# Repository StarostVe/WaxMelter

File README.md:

# WaxMelter
Induction wax melter for hot-waxing bike chains

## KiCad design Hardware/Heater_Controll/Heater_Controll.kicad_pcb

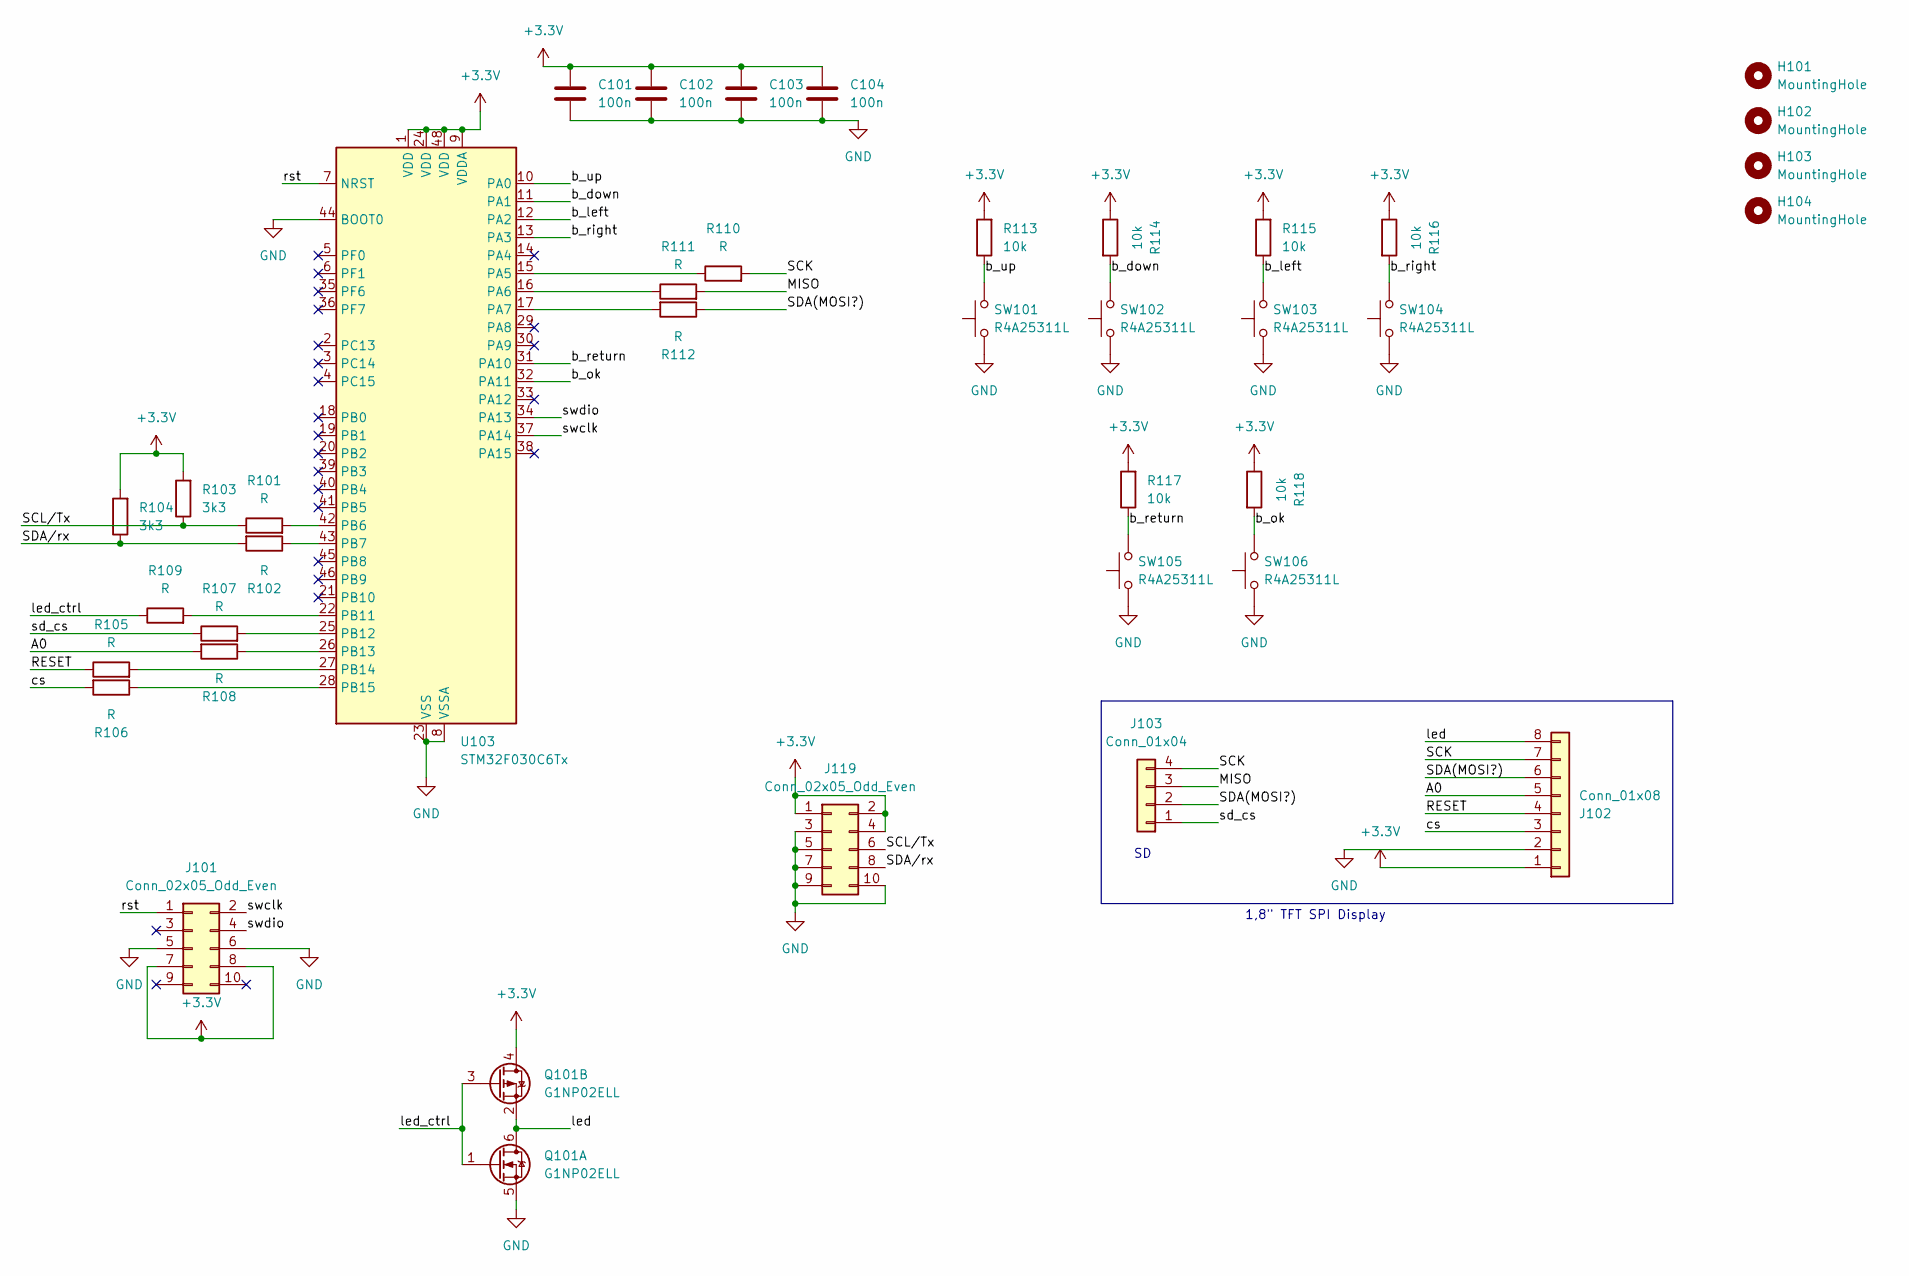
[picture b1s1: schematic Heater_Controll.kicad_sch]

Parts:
C101, C102, C103, C104: 100n; C_0603_1608Metric
H101, H102, H103, H104: MountingHole; MountingHole_3.2mm_M3_DIN965
J101, J119: Conn_02x05_Odd_Even; IDC-Header_2x05_P2.54mm_Vertical_SMD
J102: Conn_01x08; PinHeader_1x08_P2.54mm_Vertical
J103: Conn_01x04; PinHeader_1x04_P2.54mm_Vertical
Q101: G1NP02ELL; TSOT-23-6
R101, R102, R105, R106, R107, R108, R109, R110, R111, R112: R; R_0603_1608Metric
R103, R104: 3k3; R_0603_1608Metric
R113, R114, R115, R116, R117, R118: 10k; R_0603_1608Metric
SW101, SW102, SW103, SW104, SW105, SW106: R4A25311L
U103: STM32F030C6Tx; LQFP-48_7x7mm_P0.5mm

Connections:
+3.3V: C101.1, C102.1, C103.1, C104.1, J101.7, J101.8, J102.1, J119.1, J119.2, J119.4, Q101.4 (D), R103.2, R104.2, R113.2, R114.1, R115.2, R116.1, R117.2, R118.1, U103.1 (VDD), U103.9 (VDDA), U103.24 (VDD), U103.48 (VDD)
/A0: J102.5, R108.2
/MISO: J103.3, R111.2
/RESET: J102.4, R105.1
/SCK: J102.7, J103.4, R110.2
/SCL/Tx: J119.6, R101.1, R103.1
/SDA(MOSI?): J102.6, J103.2, R112.1
/SDA/rx: J119.8, R102.2, R104.1
/b_down: R114.2, SW102.2, U103.11 (PA1)
/b_left: R115.1, SW103.2, U103.12 (PA2)
/b_ok: R118.2, SW106.2, U103.32 (PA11)
/b_return: R117.1, SW105.2, U103.31 (PA10)
/b_right: R116.2, SW104.2, U103.13 (PA3)
/b_up: R113.1, SW101.2, U103.10 (PA0)
/cs: J102.3, R106.2
/led: J102.8, Q101.2 (S), Q101.6 (D)
/led_ctrl: Q101.1 (G), Q101.3 (G), R109.1
/rst: J101.1, U103.7 (NRST)
/sd_cs: J103.1, R107.1
/swclk: J101.2, U103.37 (PA14)
/swdio: J101.4, U103.34 (PA13)
GND: C101.2, C102.2, C103.2, C104.2, J101.5, J101.6, J102.2, J119.3, J119.5, J119.7, J119.9, J119.10, Q101.5 (S), SW101.1, SW102.1, SW103.1, SW104.1, SW105.1, SW106.1, U103.8 (VSSA), U103.23 (VSS), U103.44 (BOOT0), U103.47 (VSS)
unnamed: R110.1, U103.15 (PA5)
unnamed: R111.1, U103.16 (PA6)
unnamed: R112.2, U103.17 (PA7)
unnamed: R101.2, U103.42 (PB6)
unnamed: R102.1, U103.43 (PB7)
unnamed: R109.2, U103.22 (PB11)
unnamed: R107.2, U103.25 (PB12)
unnamed: R108.1, U103.26 (PB13)
unnamed: R105.2, U103.27 (PB14)
unnamed: R106.1, U103.28 (PB15)

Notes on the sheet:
1,8" TFT SPI Display

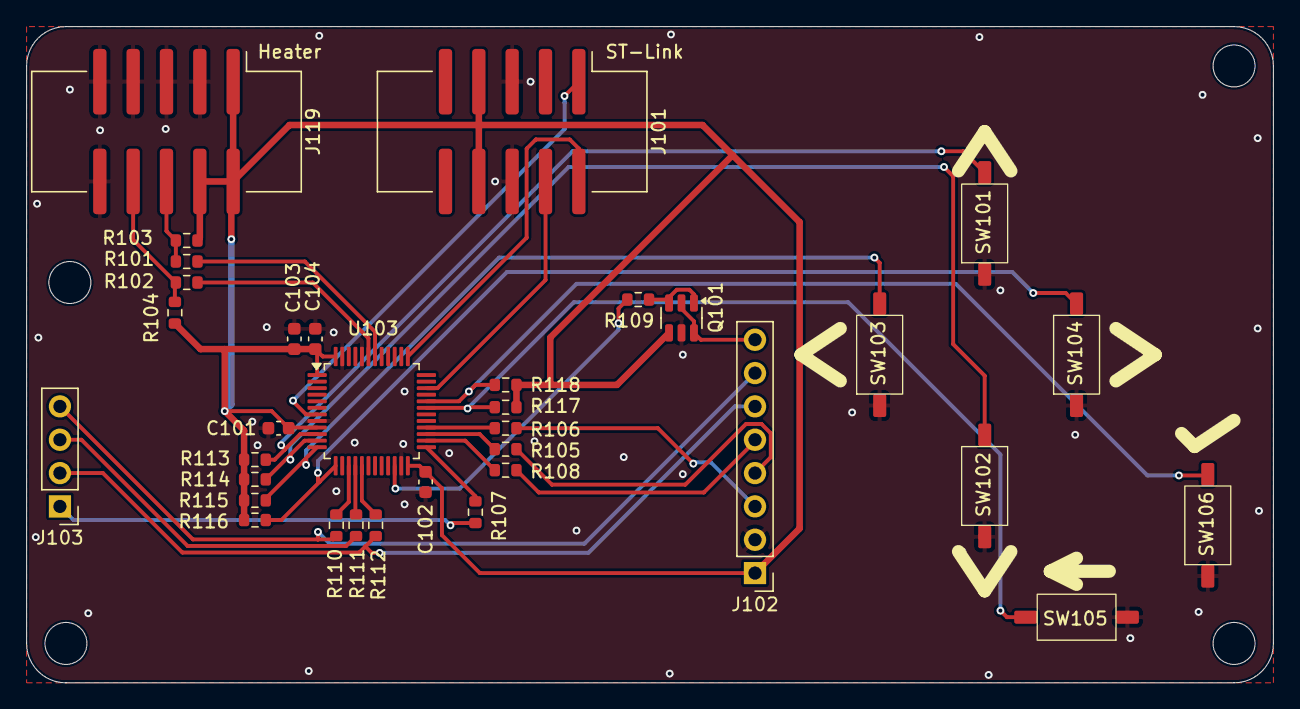
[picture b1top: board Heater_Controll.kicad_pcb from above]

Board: 2 copper layers, 95.0 x 50.0 mm, 38 parts (0 on the bottom side), 32 nets.

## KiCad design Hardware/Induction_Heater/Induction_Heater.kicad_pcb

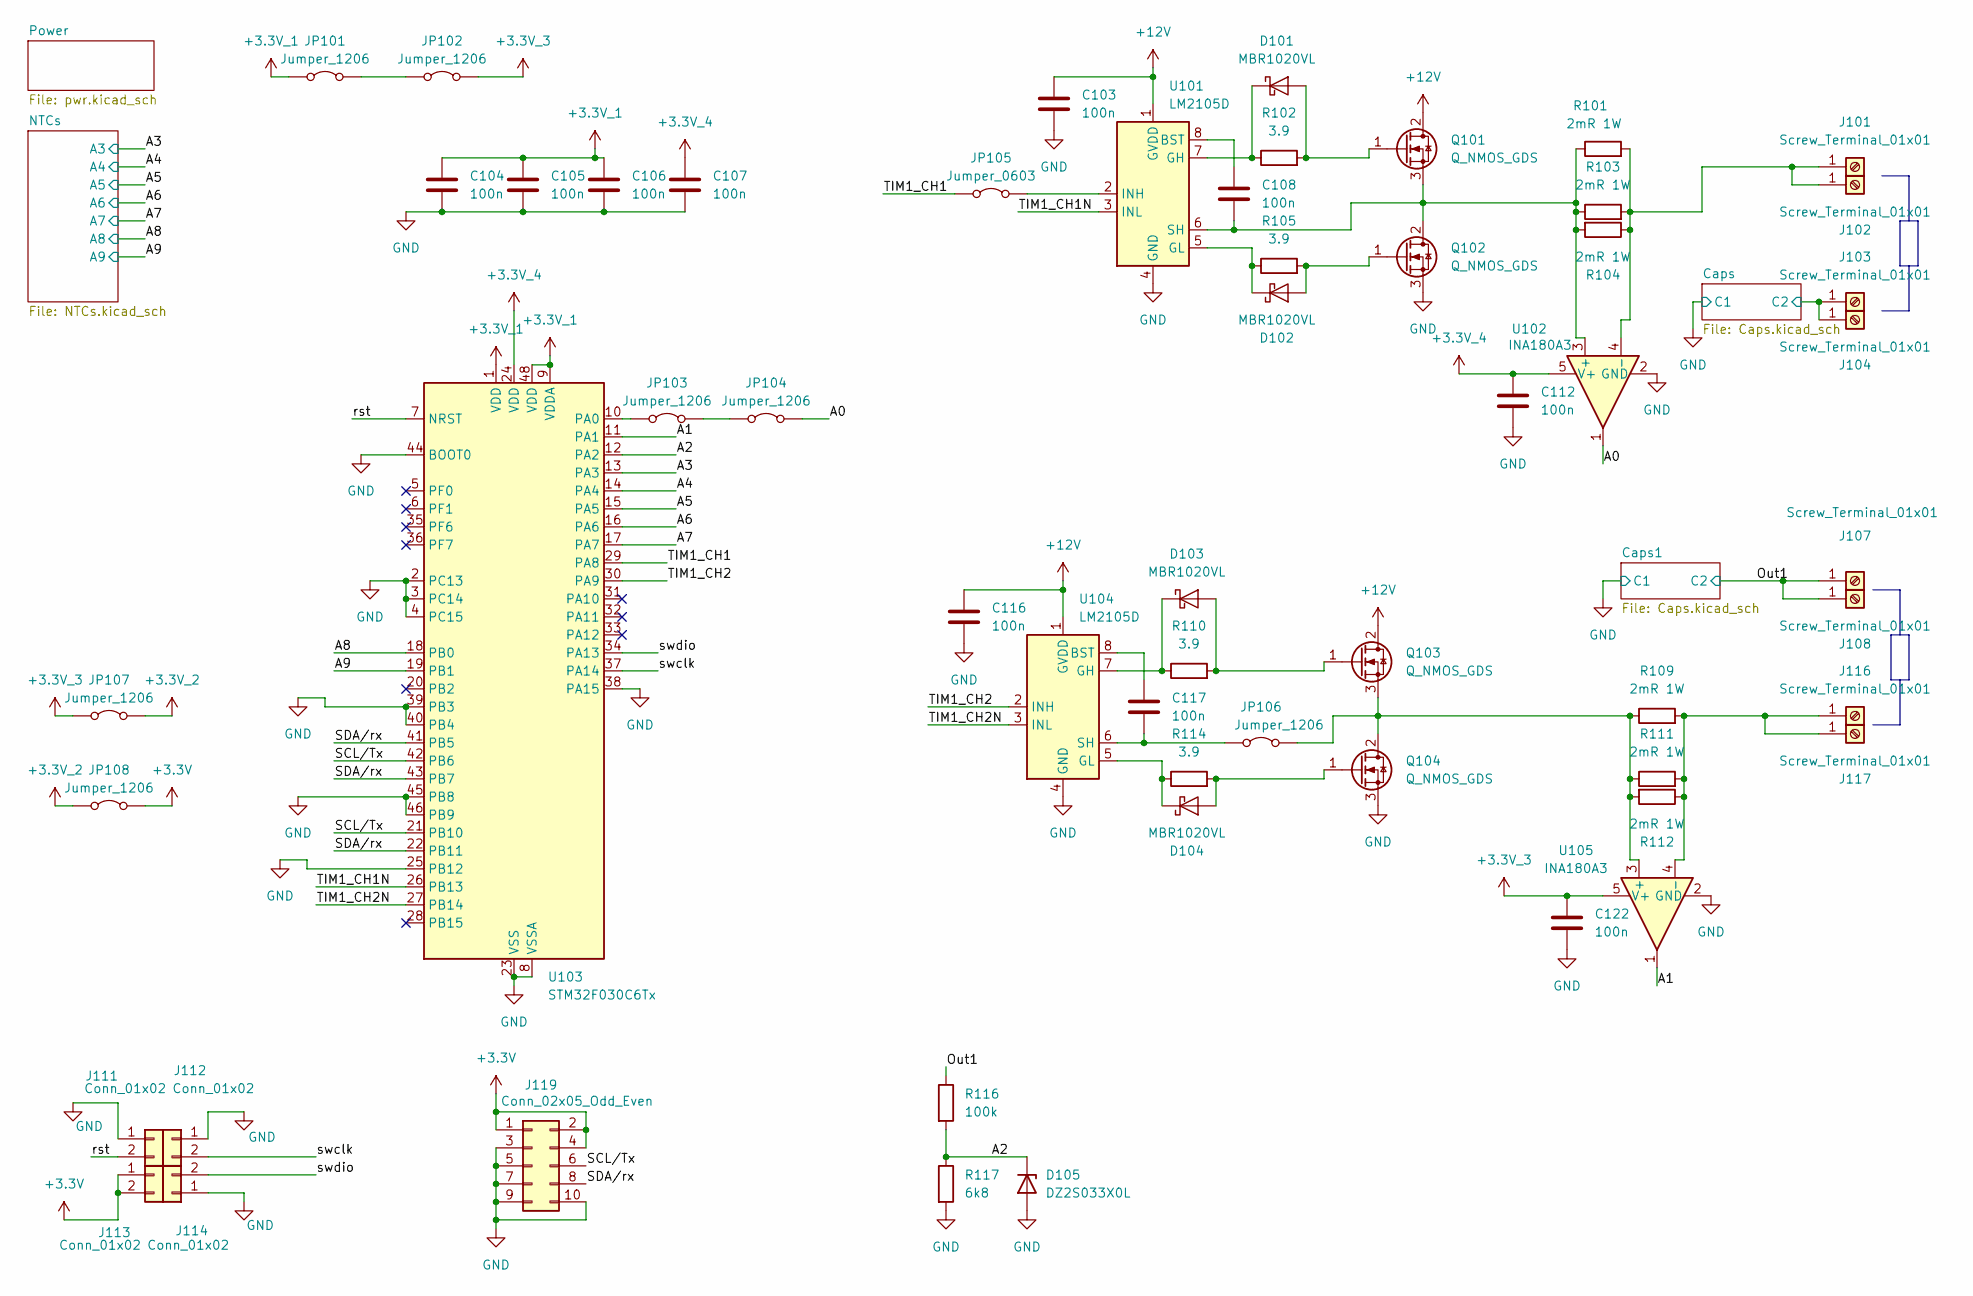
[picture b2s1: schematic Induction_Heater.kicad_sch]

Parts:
C103, C104, C105, C106, C107, C108, C112, C116, C117, C122: 100n; C_0603_1608Metric
D101, D102, D103, D104: MBR1020VL; D_SOD-123F
D105: DZ2S033X0L; D_SOD-523
J101, J102, J103, J104, J107, J108, J116, J117: Screw_Terminal_01x01; TS34056055-0440
J111, J112, J113, J114: Conn_01x02; PinHeader_1x02_P2.54mm_Vertical_SMD_Pin1Left
J119: Conn_02x05_Odd_Even; IDC-Header_2x05_P2.54mm_Vertical_SMD
JP101, JP102, JP103, JP104, JP106, JP107, JP108: Jumper_1206; R_1206_3216Metric
JP105: Jumper_0603; R_0603_1608Metric
Q101, Q102, Q103, Q104: Q_NMOS_GDS; TO-252-2
R101, R103, R104, R109, R111, R112: 2mR 1W; R_1206_3216Metric
R102, R105, R110, R114: 3.9; R_0603_1608Metric
R116: 100k; R_0603_1608Metric
R117: 6k8; R_0603_1608Metric
U101, U104: LM2105D; SOIC-8_3.9x4.9mm_P1.27mm
U102, U105: INA180A3; SOT-23-5
U103: STM32F030C6Tx; LQFP-48_7x7mm_P0.5mm

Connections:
+3.3V: J113.1, J113.2, J119.1, J119.2, J119.4, JP108.2 (B); also elsewhere on the board
+3.3V_1: C104.1, C105.1, C106.1, JP101.1 (A), U103.1 (VDD), U103.9 (VDDA), U103.48 (VDD)
+3.3V_2: JP107.2 (B), JP108.1 (A); also elsewhere on the board
+3.3V_3: C122.1, JP102.2 (B), JP107.1 (A), U105.5 (V+); also elsewhere on the board
+3.3V_4: C107.1, C112.1, U102.5 (V+), U103.24 (VDD); also elsewhere on the board
+12V: C103.1, C116.1, Q101.2 (D), Q103.2 (D), U101.1 (GVDD), U104.1 (GVDD); also elsewhere on the board
/A0: JP104.2 (B), U102.1
/A1: U103.11 (PA1), U105.1
/A2: D105.1 (K), R116.2, R117.1, U103.12 (PA2)
/A3: U103.13 (PA3); also elsewhere on the board
/A4: U103.14 (PA4); also elsewhere on the board
/A5: U103.15 (PA5); also elsewhere on the board
/A6: U103.16 (PA6); also elsewhere on the board
/A7: U103.17 (PA7); also elsewhere on the board
/A8: U103.18 (PB0); also elsewhere on the board
/A9: U103.19 (PB1); also elsewhere on the board
/Caps/C2: J103.1, J104.1; also elsewhere on the board
/Out1: J107.1, J108.1, R116.1; also elsewhere on the board
/SCL/Tx: J119.6, U103.21 (PB10), U103.42 (PB6)
/SDA/rx: J119.8, U103.22 (PB11), U103.41 (PB5), U103.43 (PB7)
/TIM1_CH1: JP105.1 (A), U103.29 (PA8)
/TIM1_CH1N: U101.3 (INL), U103.26 (PB13)
/TIM1_CH2: U103.30 (PA9), U104.2 (INH)
/TIM1_CH2N: U103.27 (PB14), U104.3 (INL)
/rst: J111.2, U103.7 (NRST)
/swclk: J112.2, U103.37 (PA14)
/swdio: J114.2, U103.34 (PA13)
GND: C103.2, C104.2, C105.2, C106.2, C107.2, C112.2, C116.2, C122.2, D105.2 (A), J111.1, J112.1, J114.1, J119.3, J119.5, J119.7, J119.9, J119.10, Q102.3 (S), Q104.3 (S), R117.2, U101.4 (GND), U102.2 (GND), U103.2 (PC13), U103.3 (PC14), U103.4 (PC15), U103.8 (VSSA), U103.23 (VSS), U103.25 (PB12), U103.38 (PA15), U103.39 (PB3), U103.40 (PB4), U103.44 (BOOT0), U103.45 (PB8), U103.46 (PB9), U103.47 (VSS), U104.4 (GND), U105.2 (GND); also elsewhere on the board
unnamed: D101.2 (A), Q101.1 (G), R102.2
unnamed: D101.1 (K), R102.1, U101.7 (GH)
unnamed: D102.2 (A), Q102.1 (G), R105.2
unnamed: D102.1 (K), R105.1, U101.5 (GL)
unnamed: D103.2 (A), Q103.1 (G), R110.2
unnamed: D103.1 (K), R110.1, U104.7 (GH)
unnamed: D104.2 (A), Q104.1 (G), R114.2
unnamed: D104.1 (K), R114.1, U104.5 (GL)
unnamed: J101.1, J102.1, R101.2, R103.2, R104.1, U102.4 (-)
unnamed: J116.1, J117.1, R109.2, R111.2, R112.1, U105.4 (-)
unnamed: JP101.2 (B), JP102.1 (A)
unnamed: JP103.1 (A), U103.10 (PA0)
unnamed: JP103.2 (B), JP104.1 (A)
unnamed: JP105.2 (B), U101.2 (INH)
unnamed: C117.2, JP106.1 (A), U104.6 (SH)
unnamed: JP106.2 (B), Q103.3 (S), Q104.2 (D), R109.1, R111.1, R112.2, U105.3 (+)
unnamed: C108.2, Q101.3 (S), Q102.2 (D), R101.1, R103.1, R104.2, U101.6 (SH), U102.3 (+)
unnamed: C108.1, U101.8 (BST)
unnamed: C117.1, U104.8 (BST)

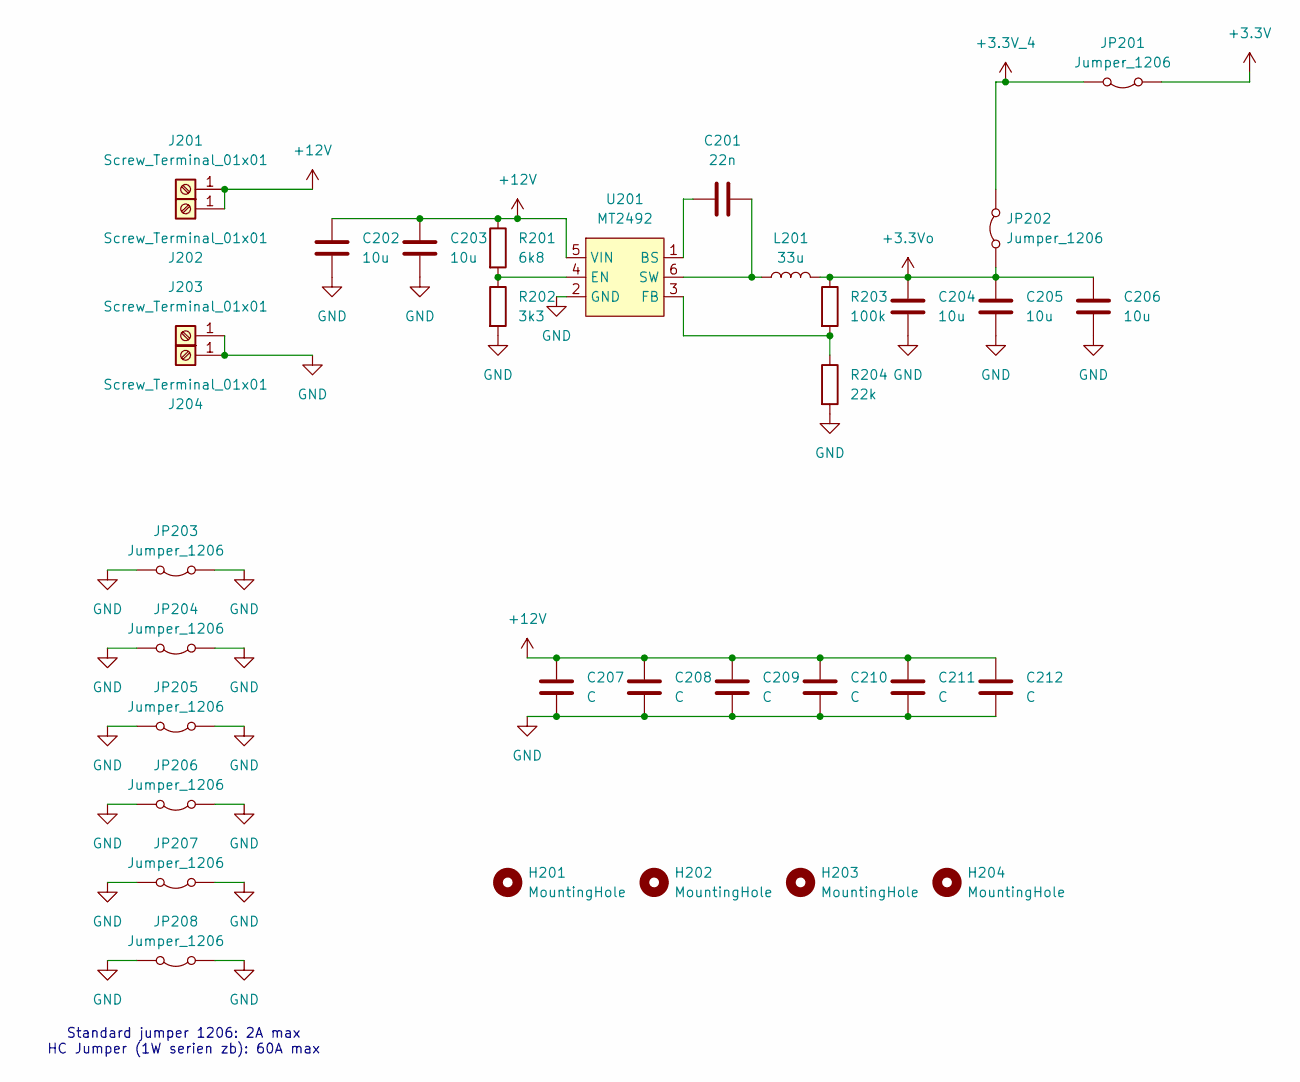
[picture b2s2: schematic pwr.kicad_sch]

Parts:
C201: 22n; C_0603_1608Metric
C202, C203, C204, C205, C206: 10u; C_0603_1608Metric
C207, C208, C209, C210, C211, C212: C; C_1206_3216Metric
H201, H202, H203, H204: MountingHole; MountingHole_3.2mm_M3_DIN965
J201, J202, J203, J204: Screw_Terminal_01x01; TS34056055-0440
JP201, JP202, JP203, JP204, JP205, JP206, JP207, JP208: Jumper_1206; R_1206_3216Metric
L201: 33u; L_APV_ANR4030
R201: 6k8; R_0603_1608Metric
R202: 3k3; R_0603_1608Metric
R203: 100k; R_0603_1608Metric
R204: 22k; R_0603_1608Metric
U201: MT2492; SOT-23-6

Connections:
+3.3V: JP201.1 (A); also elsewhere on the board
+3.3V_4: JP201.2 (B), JP202.2 (B); also elsewhere on the board
+3.3Vo: C204.1, C205.1, C206.1, JP202.1 (A), L201.2, R203.1
+12V: C202.1, C203.1, C207.1, C208.1, C209.1, C210.1, C211.1, C212.1, J201.1, J202.1, R201.1, U201.5 (VIN); also elsewhere on the board
GND: C202.2, C203.2, C204.2, C205.2, C206.2, C207.2, C208.2, C209.2, C210.2, C211.2, C212.2, J203.1, J204.1, JP203.1 (A), JP203.2 (B), JP204.1 (A), JP204.2 (B), JP205.1 (A), JP205.2 (B), JP206.1 (A), JP206.2 (B), JP207.1 (A), JP207.2 (B), JP208.1 (A), JP208.2 (B), R202.2, R204.2, U201.2 (GND); also elsewhere on the board
unnamed: C201.1, U201.1 (BS)
unnamed: R201.2, R202.1, U201.4 (EN)
unnamed: R203.2, R204.1, U201.3 (FB)
unnamed: C201.2, L201.1, U201.6 (SW)

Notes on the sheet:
Standard jumper 1206: 2A max HC Jumper (1W serien zb): 60A max

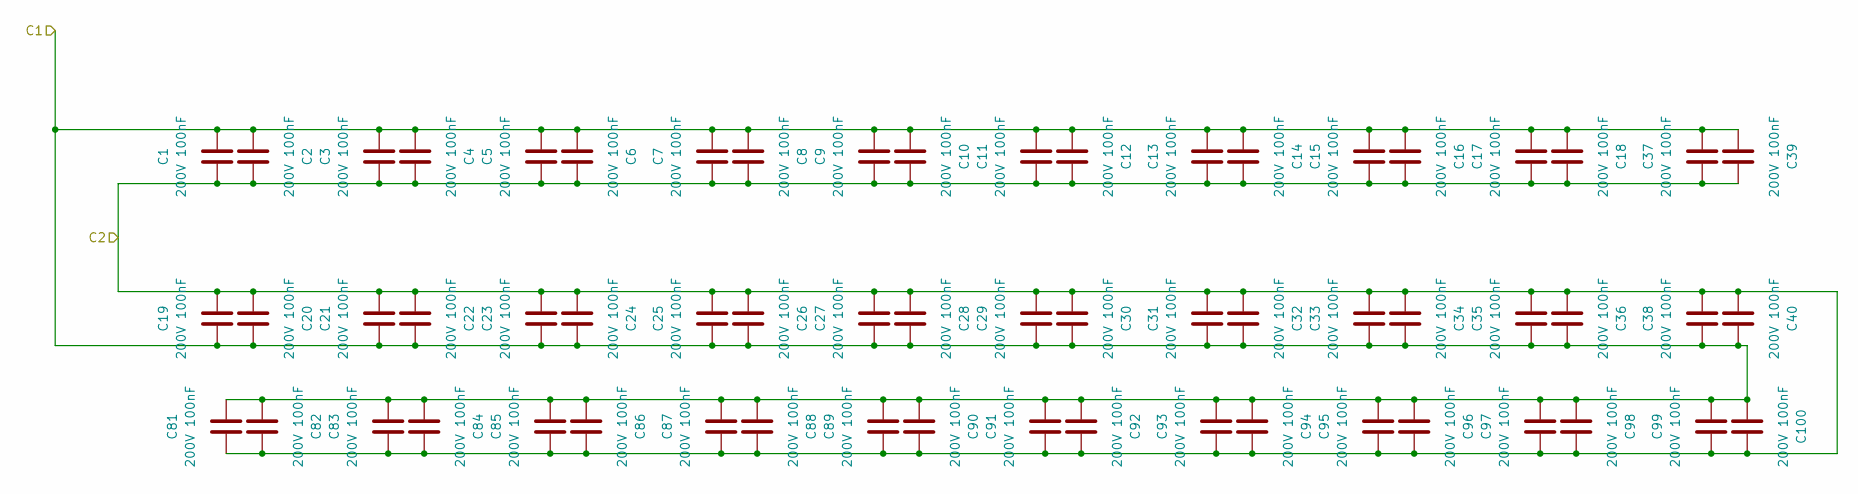
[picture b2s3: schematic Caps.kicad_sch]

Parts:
C1, C2, C3, C4, C5, C6, C7, C8, C9, C10, C11, C12, C13, C14, C15, C16, C17, C18, C19, C20, C21, C22, C23, C24, C25, C26, C27, C28, C29, C30, C31, C32, C33, C34, C35, C36, C37, C38, C39, C40, C81, C82, C83, C84, C85, C86, C87, C88, C89, C90, C91, C92, C93, C94, C95, C96, C97, C98, C99, C100: 200V 100nF; C_0805_2012Metric

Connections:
/Caps/C2: C1.1, C2.1, C3.1, C4.1, C5.1, C6.1, C7.1, C8.1, C9.1, C10.1, C11.1, C12.1, C13.1, C14.1, C15.1, C16.1, C17.1, C18.1, C19.2, C20.2, C21.2, C22.2, C23.2, C24.2, C25.2, C26.2, C27.2, C28.2, C29.2, C30.2, C31.2, C32.2, C33.2, C34.2, C35.2, C36.2, C37.1, C38.2, C39.1, C40.2, C81.1, C82.1, C83.1, C84.1, C85.1, C86.1, C87.1, C88.1, C89.1, C90.1, C91.1, C92.1, C93.1, C94.1, C95.1, C96.1, C97.1, C98.1, C99.1, C100.1; also elsewhere on the board
GND: C1.2, C2.2, C3.2, C4.2, C5.2, C6.2, C7.2, C8.2, C9.2, C10.2, C11.2, C12.2, C13.2, C14.2, C15.2, C16.2, C17.2, C18.2, C19.1, C20.1, C21.1, C22.1, C23.1, C24.1, C25.1, C26.1, C27.1, C28.1, C29.1, C30.1, C31.1, C32.1, C33.1, C34.1, C35.1, C36.1, C37.2, C38.1, C39.2, C40.1, C81.2, C82.2, C83.2, C84.2, C85.2, C86.2, C87.2, C88.2, C89.2, C90.2, C91.2, C92.2, C93.2, C94.2, C95.2, C96.2, C97.2, C98.2, C99.2, C100.2; also elsewhere on the board

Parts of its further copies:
C41, C42, C43, C44, C45, C46, C47, C48, C49, C50, C51, C52, C53, C54, C55, C56, C57, C58, C59, C60, C61, C62, C63, C64, C65, C66, C67, C68, C69, C70, C71, C72, C73, C74, C75, C76, C77, C78, C79, C80, C101, C102, C109, C110, C111, C113, C114, C115, C118, C119, C120, C121, C123, C124, C125, C126, C127, C128, C129, C130: 200V 100nF; C_0805_2012Metric

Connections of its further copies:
/Out1: C41.1, C42.2, C43.1, C44.2, C45.1, C46.2, C47.1, C48.2, C49.1, C50.2, C51.1, C52.2, C53.1, C54.2, C55.1, C56.2, C57.1, C58.2, C59.1, C60.2, C61.1, C62.2, C63.1, C64.2, C65.1, C66.2, C67.1, C68.2, C69.1, C70.2, C71.1, C72.2, C73.1, C74.2, C75.1, C76.2, C77.1, C78.2, C79.1, C80.2, C101.1, C102.1, C109.1, C110.1, C111.1, C113.1, C114.1, C115.1, C118.1, C119.1, C120.1, C121.1, C123.1, C124.1, C125.1, C126.1, C127.1, C128.1, C129.1, C130.1; also elsewhere on the board
GND: C41.2, C42.1, C43.2, C44.1, C45.2, C46.1, C47.2, C48.1, C49.2, C50.1, C51.2, C52.1, C53.2, C54.1, C55.2, C56.1, C57.2, C58.1, C59.2, C60.1, C61.2, C62.1, C63.2, C64.1, C65.2, C66.1, C67.2, C68.1, C69.2, C70.1, C71.2, C72.1, C73.2, C74.1, C75.2, C76.1, C77.2, C78.1, C79.2, C80.1, C101.2, C102.2, C109.2, C110.2, C111.2, C113.2, C114.2, C115.2, C118.2, C119.2, C120.2, C121.2, C123.2, C124.2, C125.2, C126.2, C127.2, C128.2, C129.2, C130.2; also elsewhere on the board

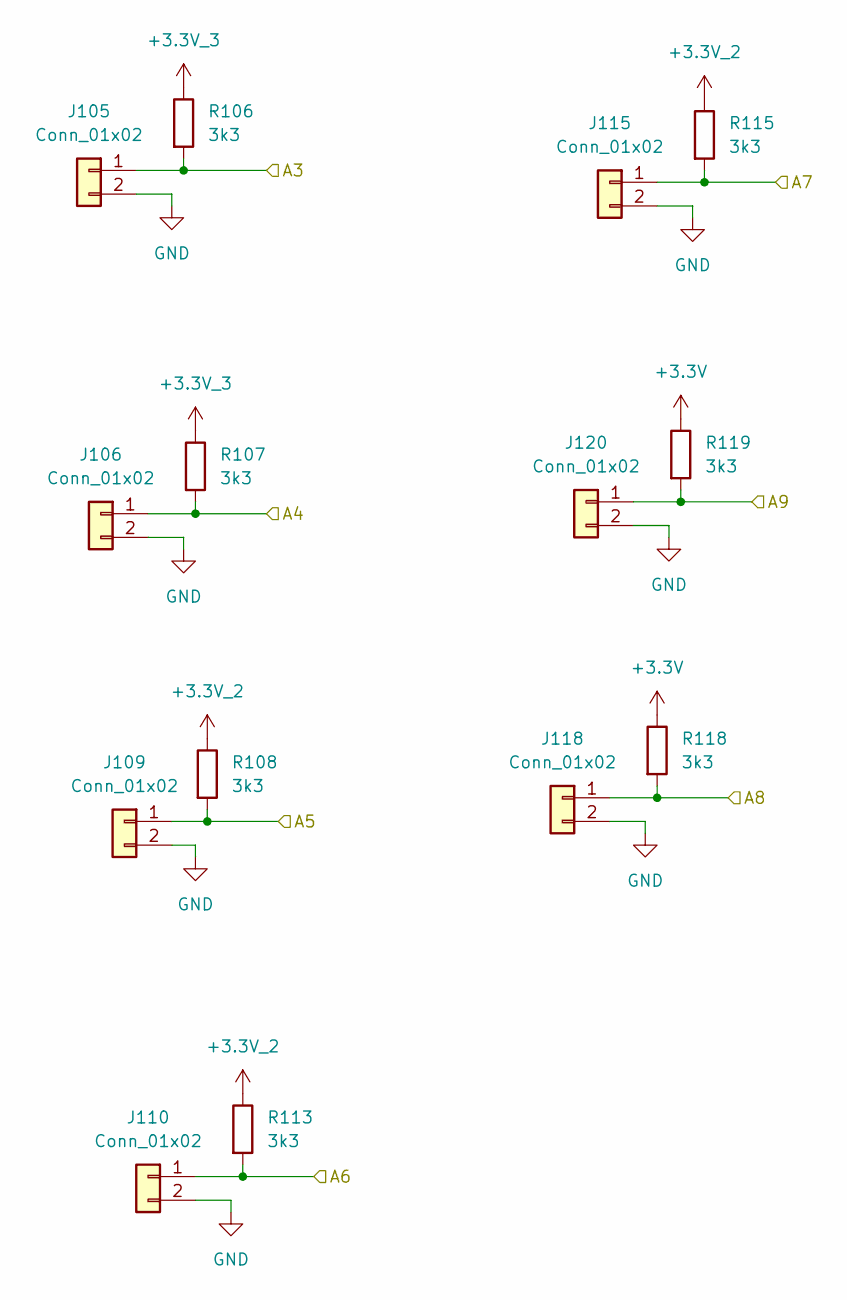
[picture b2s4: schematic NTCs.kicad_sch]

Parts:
J105, J106, J109, J110, J115, J118, J120: Conn_01x02; PinHeader_1x02_P2.54mm_Vertical_SMD_Pin1Left
R106, R107, R108, R113, R115, R118, R119: 3k3; R_0603_1608Metric

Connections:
+3.3V: R118.1, R119.1; also elsewhere on the board
+3.3V_2: R108.1, R113.1, R115.1; also elsewhere on the board
+3.3V_3: R106.1, R107.1; also elsewhere on the board
/A3: J105.1, R106.2; also elsewhere on the board
/A4: J106.1, R107.2; also elsewhere on the board
/A5: J109.1, R108.2; also elsewhere on the board
/A6: J110.1, R113.2; also elsewhere on the board
/A7: J115.1, R115.2; also elsewhere on the board
/A8: J118.1, R118.2; also elsewhere on the board
/A9: J120.1, R119.2; also elsewhere on the board
GND: J105.2, J106.2, J109.2, J110.2, J115.2, J118.2, J120.2; also elsewhere on the board

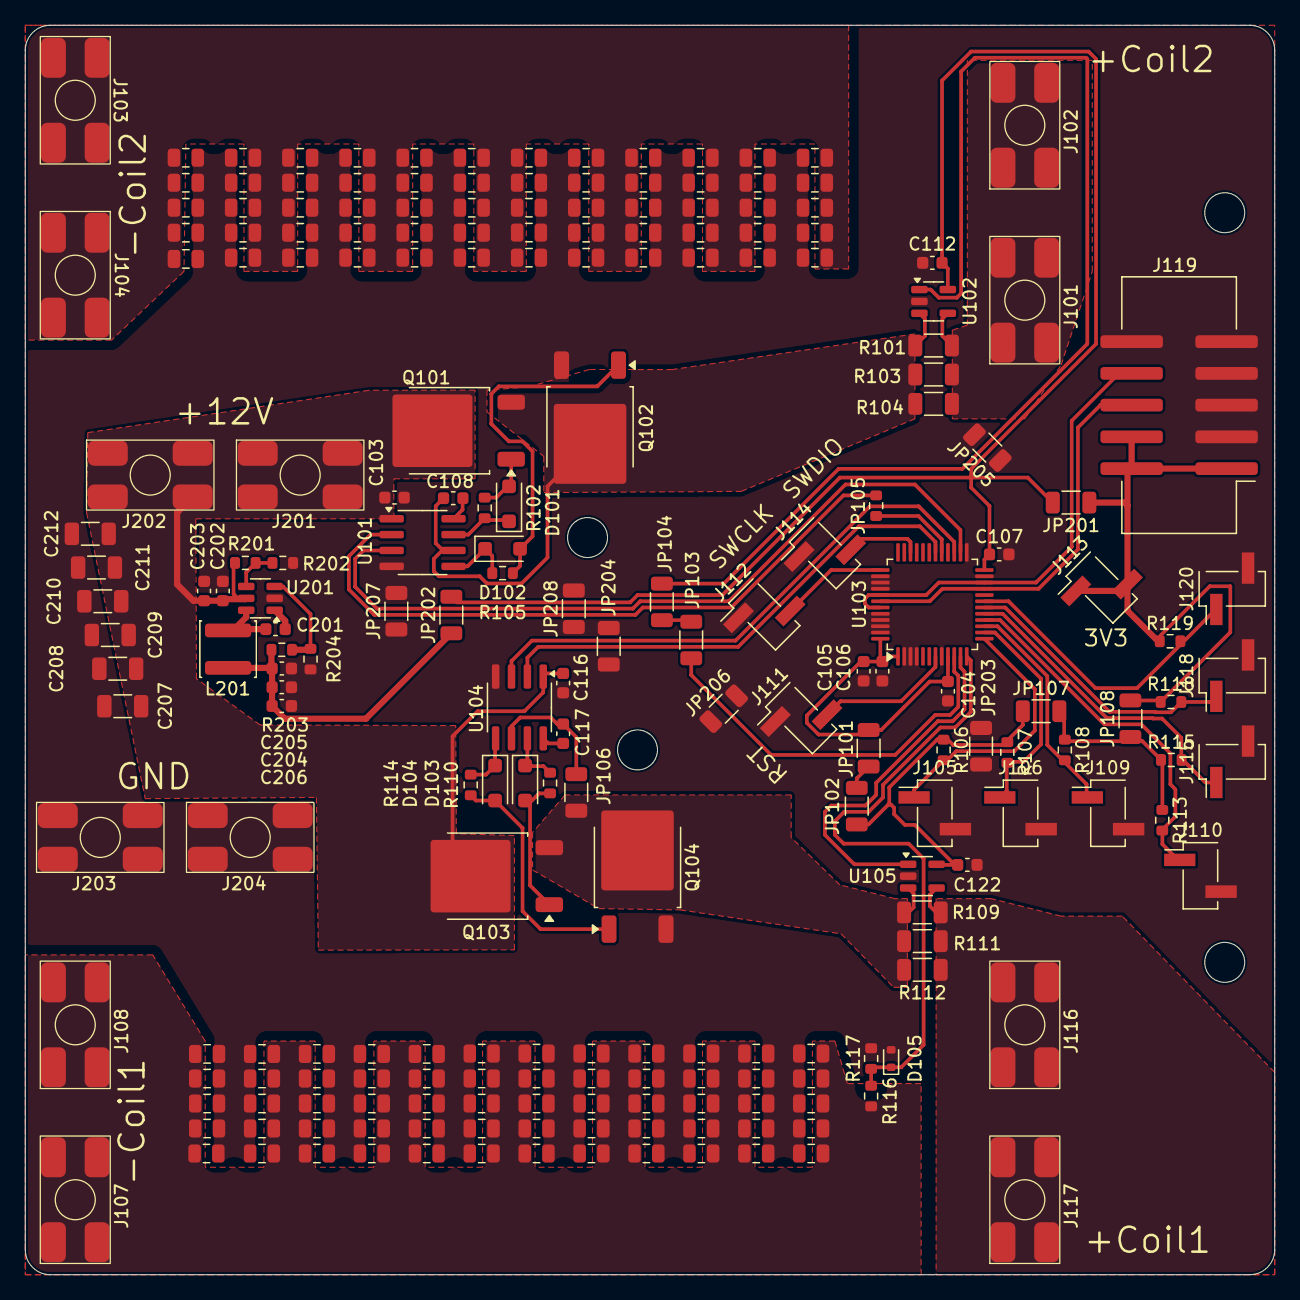
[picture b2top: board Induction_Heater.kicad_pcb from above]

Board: 2 copper layers, 100.0 x 100.0 mm, 225 parts (0 on the bottom side), 52 nets.
